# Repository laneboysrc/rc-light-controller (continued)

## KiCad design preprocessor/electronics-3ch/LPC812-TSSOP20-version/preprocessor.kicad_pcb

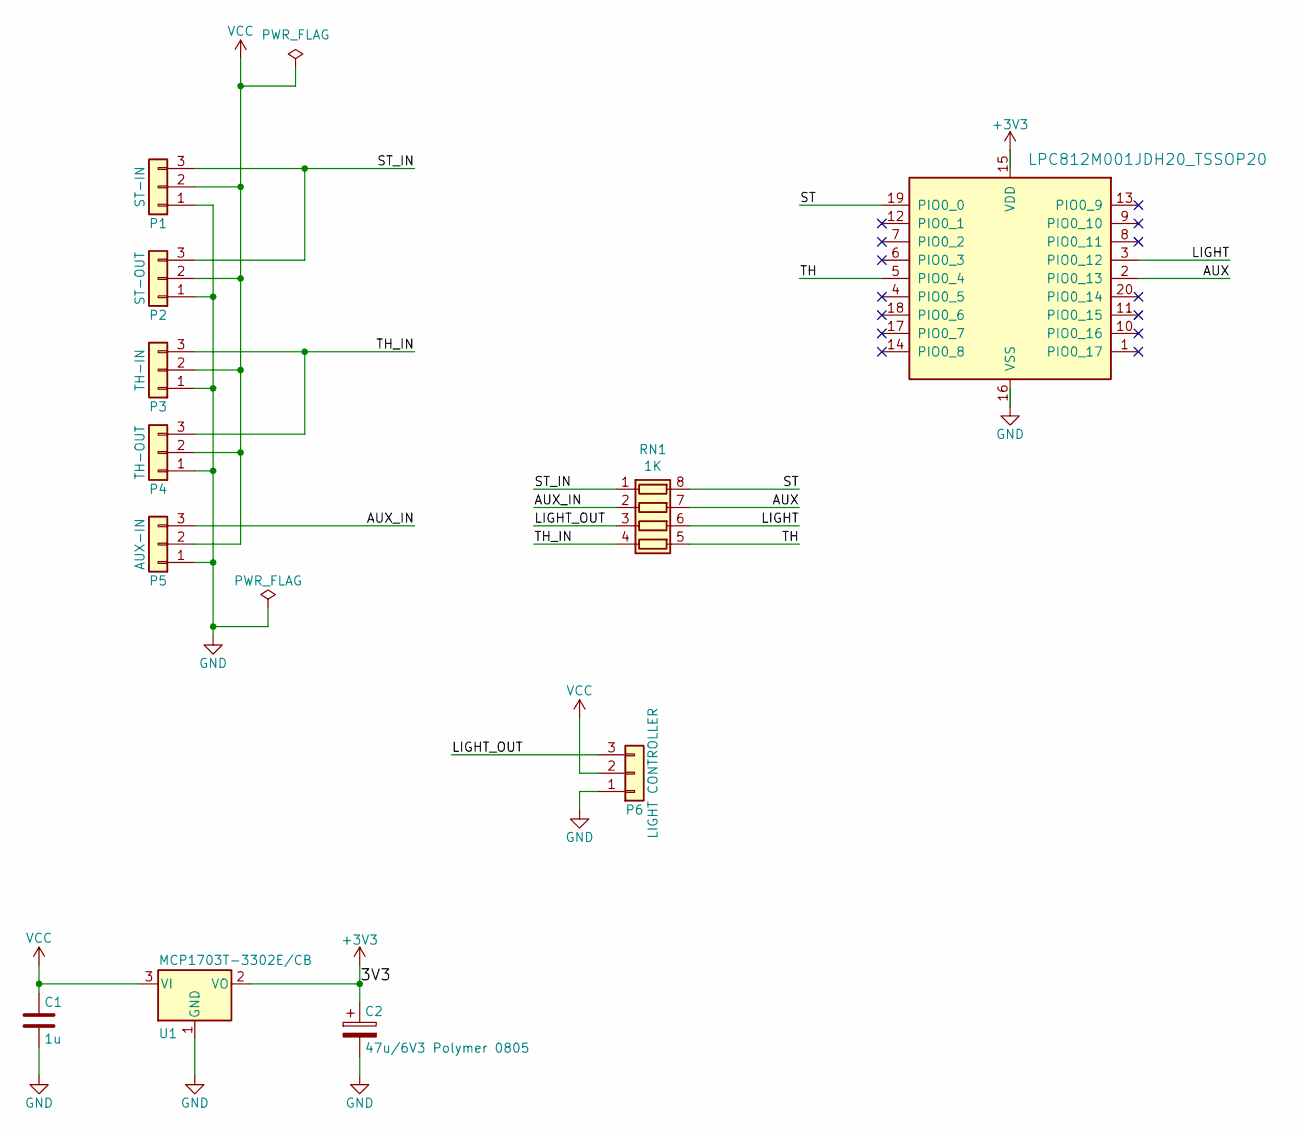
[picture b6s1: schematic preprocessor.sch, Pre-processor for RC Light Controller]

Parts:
C1: 1u; C_0805_2012Metric_Pad1.15x1.40mm_HandSolder
C2: 47u/6V3 Polymer 0805; C_0805_2012Metric_Pad1.15x1.40mm_HandSolder
P1: ST-IN; Pin_Header_Straight_1x03_Pitch2.54mm
P2: ST-OUT; Pin_Header_Straight_1x03_Pitch2.54mm
P3: TH-IN; Pin_Header_Straight_1x03_Pitch2.54mm
P4: TH-OUT; Pin_Header_Straight_1x03_Pitch2.54mm
P5: AUX-IN; Pin_Header_Straight_1x03_Pitch2.54mm
P6: LIGHT CONTROLLER; Pin_Header_Straight_1x03_Pitch2.54mm
RN1: 1K; R_Array_Convex_4x0603
U1: MCP1703T-3302E/CB; SOT-23W
U2: LPC812M001JDH20_TSSOP20; TSSOP-20_4.4x6.5mm_P0.65mm

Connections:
+3V3: C2.1, U1.2 (VO), U2.15 (VDD)
/AUX: RN1.7 (R2.2), U2.2 (PIO0_13)
/AUX_IN: P5.3, RN1.2 (R2.1)
/LIGHT: RN1.6 (R3.2), U2.3 (PIO0_12)
/LIGHT_OUT: P6.3, RN1.3 (R3.1)
/ST: RN1.8 (R1.2), U2.19 (PIO0_0)
/ST_IN: P1.3, P2.3, RN1.1 (R1.1)
/TH: RN1.5 (R4.2), U2.5 (PIO0_4)
/TH_IN: P3.3, P4.3, RN1.4 (R4.1)
GND: C1.2, C2.2, P1.1, P2.1, P3.1, P4.1, P5.1, P6.1, U1.1 (GND), U2.16 (VSS)
VCC: C1.1, P1.2, P2.2, P3.2, P4.2, P5.2, P6.2, U1.3 (VI)

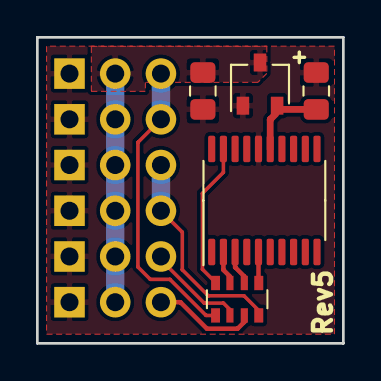
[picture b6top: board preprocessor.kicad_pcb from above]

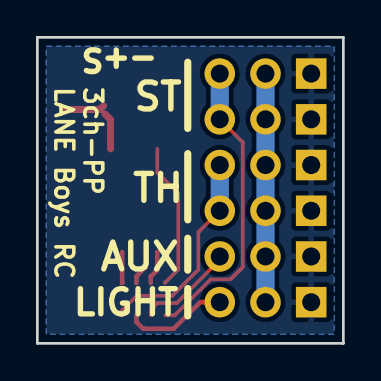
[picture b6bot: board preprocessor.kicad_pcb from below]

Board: 2 copper layers, 17.0 x 17.0 mm, 11 parts (6 on the bottom side), 11 nets.
